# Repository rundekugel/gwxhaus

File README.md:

# gwxhaus
## Greenhouse Controller

*It's just started, not finished.*

Open hardware and firmware to control a greenhouse heating and cooling. Depends on temperature, humidity, wind and time.

An ESP32 controls the motor-controller and reads sensor data.

### Sensors
- Temperature in/out
- Humidity in/out
- Wind
- Soil moisture

There can be a lot of settings depending on sensor values and time.

### Actors
- Motors to open/close the windows
- Valves to control water
- Relais to control heating

The ESP32 is connected via another ESP32, ESP8266 or RaspberryPi to the WWW. Via mqtt the sensor data and actor positions are stored in a database and can be viewd in charts.

Optional, password protected, it's possible to change the settings and manually control the actors.

If any sensor values are out of range, or power fails, there can be messages sent via email, telegram, SMS, telephone (voip), or other channels.

Weather forecast data from Deutscher Wetterdienst https://dwd.api.bund.dev/ can be used to protect windows against storm or hail.

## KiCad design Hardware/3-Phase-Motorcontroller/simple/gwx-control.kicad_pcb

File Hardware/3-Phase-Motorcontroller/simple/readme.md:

# gwx-control-motor
## Simple motor controller

Created to control a 3 phase motor to open/close windows of a greenhouse
Created with Eagle Version 7.7

Features:
- switch off motor, if window arrived at end position 
- stop for about 3 seconds, if direction changes, to prevent too high current, which could destroy power switches.

Input: 
- motor on/off
- up/down
- switches for end positions

Output:
- +/- for optocoupler of power motor switcher. Can control DC and AC, 1 to 3 phase motors.
- +/- for direction switch relais

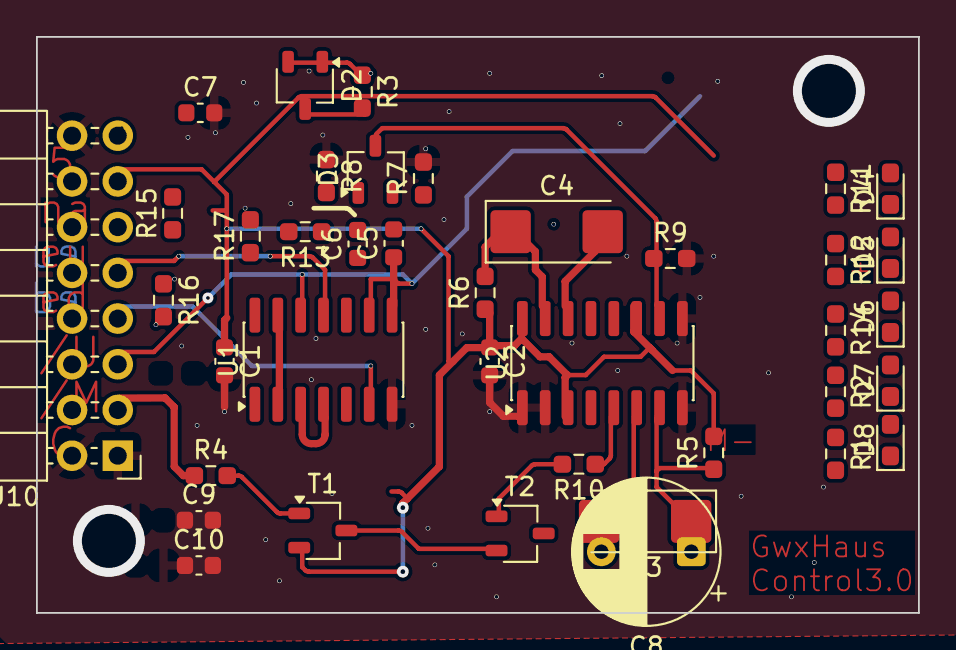
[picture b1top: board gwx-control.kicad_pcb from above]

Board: 2 copper layers, 49.0 x 32.0 mm, 39 parts (0 on the bottom side), 23 nets.

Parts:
C1, C2, C9, C10: 100n; C_0603_1608Metric
C3, C4: 47µ; CP_EIA-6032-28_Kemet-C_HandSolder
C5, C6: 1n; C_0603_1608Metric
C7: 1µF; C_0603_1608Metric
C8: 47µ; CP_Radial_D8.0mm_P5.00mm
D2, D3: BAT54C; TSOT-23
D4, D5, D6, D7, D8: LED_ESML0603; LED_0603_1608Metric_Pad1.05x0.95mm_HandSolder
J10: Conn_02x08_Odd_Even; PinHeader_2x08_P2.54mm_Horizontal
R1, R2, R3, R11, R12, R13, R14, R17: 4k7; R_0603_1608Metric_Pad0.98x0.95mm_HandSolder
R4, R7, R8, R10: 10k; R_0603_1608Metric_Pad0.98x0.95mm_HandSolder
R5, R9: 47k; R_0603_1608Metric_Pad0.98x0.95mm_HandSolder
R6: R-EU_R0603; R_0603_1608Metric_Pad0.98x0.95mm_HandSolder
R15, R16: 100R; R_0603_1608Metric_Pad0.98x0.95mm_HandSolder
T1, T2: BC850; TSOT-23
U1: 74LS02; SOIC-14_3.9x8.7mm_P1.27mm
U2: 74LS123; SOIC-16_3.9x9.9mm_P1.27mm

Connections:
/UP: C6.1, R13.1
//END_DOWN: C10.1, D8.1 (K), R16.1, U1.6
//END_UP: C9.2, D7.1 (K), R15.1, R17.1, U1.11
//MOTOR_OK: D5.1 (K), R10.1, U2.5 (Q)
//MOTOR_ON: D4.1 (K), J10.3, R4.1
//OK: J10.13, U1.1
//UP: C5.1, D2.1 (A1), D2.2 (A2), D6.1 (K), J10.5, R3.1, U1.8, U1.9, U1.12
GND: C1.2, C2.2, C7.2, C9.1, C10.2, J10.1, J10.2, J10.16, R7.2, R8.1, R9.2, U1.7 (GND), U2.1 (A), U2.2 (B), U2.8 (GND), U2.9 (A)
unnamed: C5.2, C6.2, R7.1, R8.2
unnamed: D3.3 (CC), R9.1, U2.10 (B)
unnamed: D4.2 (A), R11.1
unnamed: D5.2 (A), R12.1
unnamed: D6.2 (A), R14.1
unnamed: D7.2 (A), R2.1
unnamed: D8.2 (A), R1.1
unnamed: J10.7, R16.2
unnamed: J10.9, R15.2
unnamed: U1.3, U1.4
unnamed: U1.5, U1.10
unnamed: U1.2, U1.13
unnamed: R6.2, U2.15 (RCext)
unnamed: R5.1, U2.7 (RCext)
VCC: C1.1, C2.1, C7.1, D2.3 (CC), J10.15, R1.2, R2.2, R3.2, R5.2, R6.1, R11.2, R12.2, R13.2, R14.2, R17.2, U2.11 (Clr), U2.16 (VCC)

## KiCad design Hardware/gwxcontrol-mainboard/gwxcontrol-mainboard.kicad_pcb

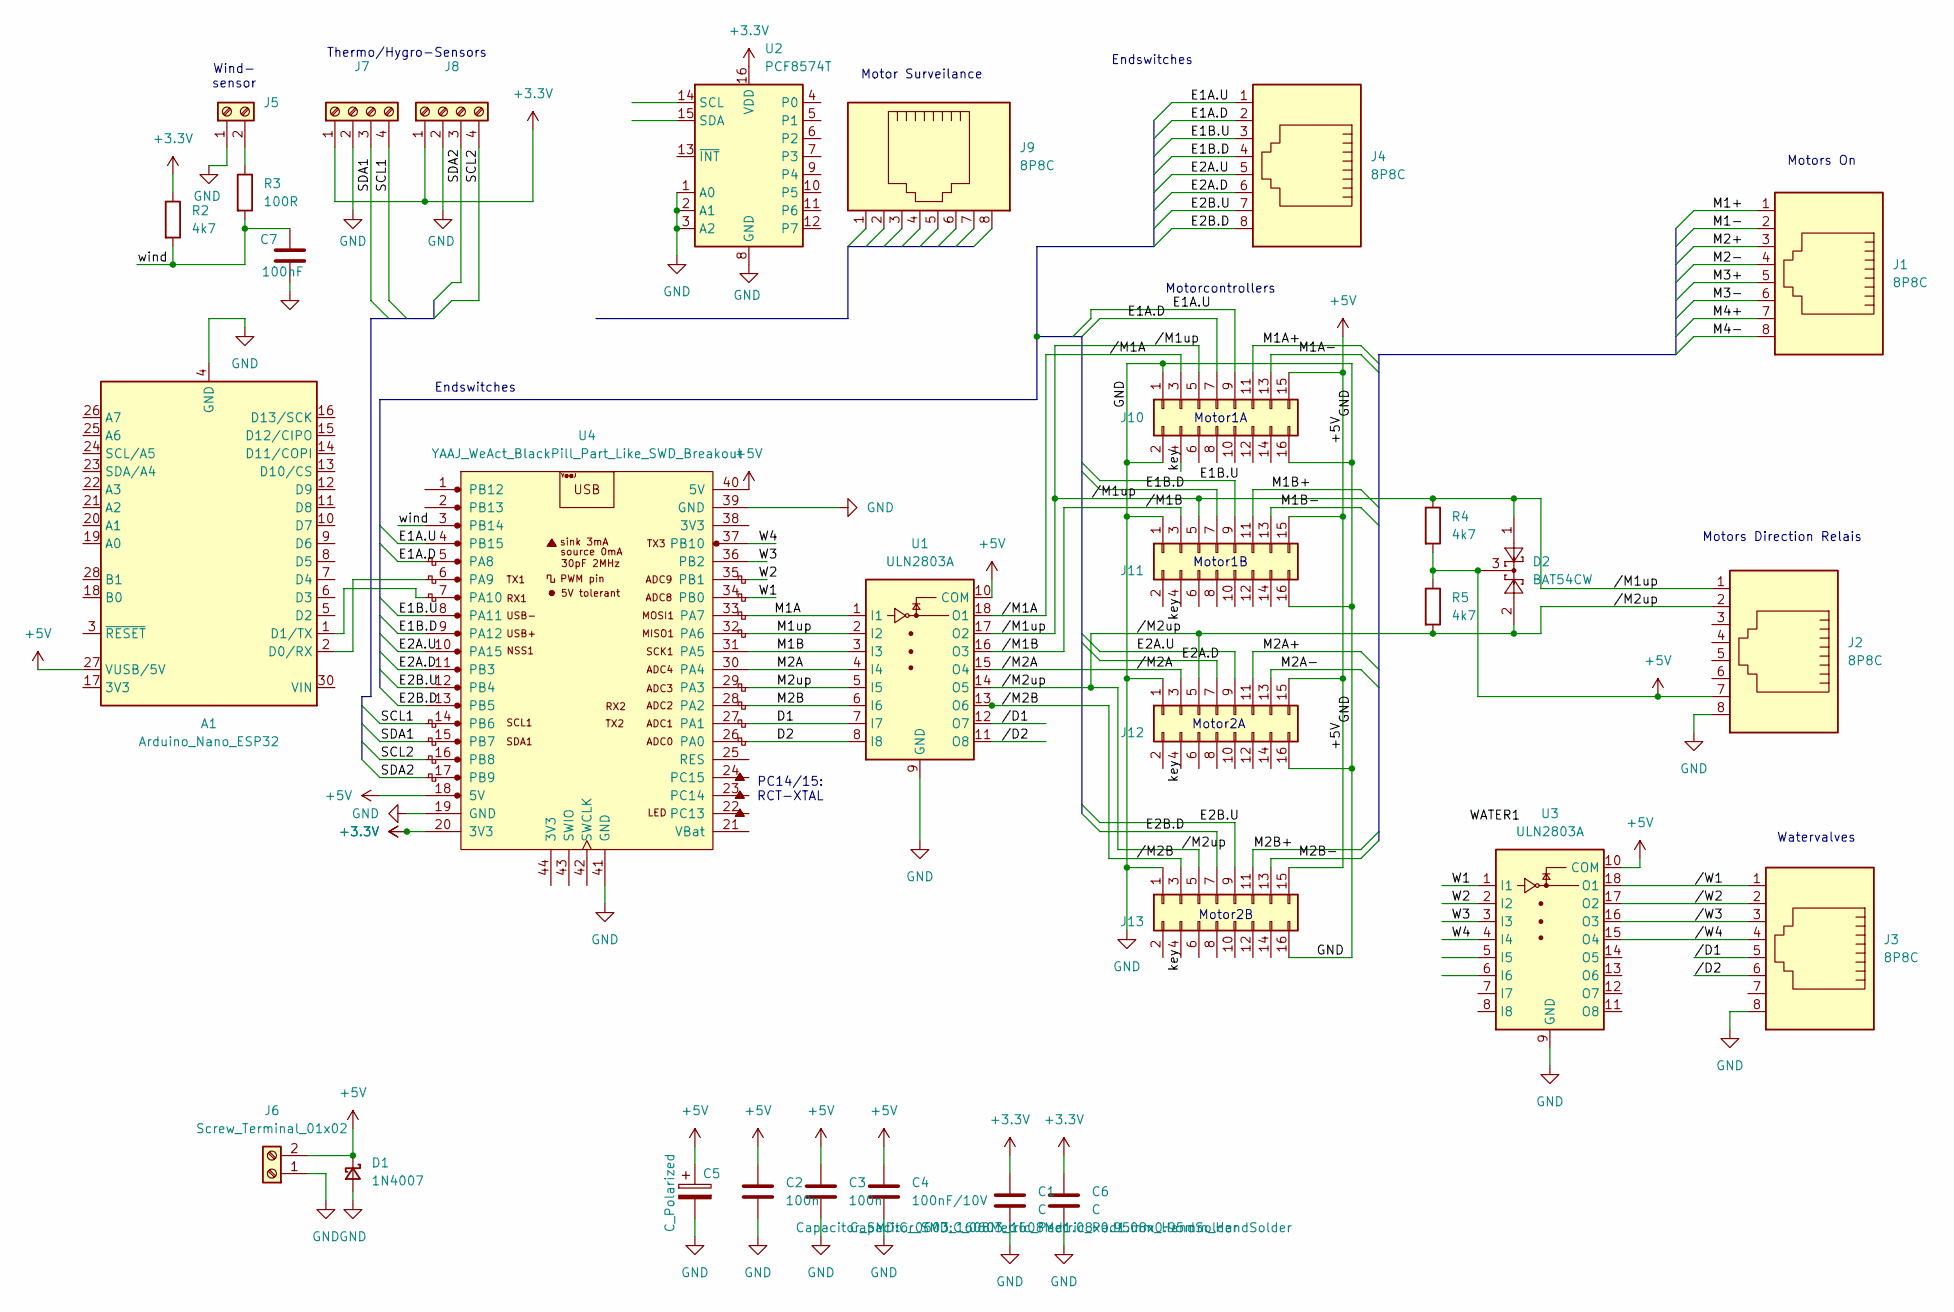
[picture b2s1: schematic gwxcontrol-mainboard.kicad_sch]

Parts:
A1: Arduino_Nano_ESP32; Arduino_Nano
C1, C6: C; C_0603_1608Metric_Pad1.08x0.95mm_HandSolder
C2, C3: 100n; C_0603_1608Metric_Pad1.08x0.95mm_HandSolder
C4: 100nF/10V; C_0603_1608Metric_Pad1.08x0.95mm_HandSolder
C5: C_Polarized; CP_Radial_D12.5mm_P5.00mm
C7: 100nF; C_0603_1608Metric_Pad1.08x0.95mm_HandSolder
D1: 1N4007; D_DO-41_SOD81_P10.16mm_Horizontal
D2: BAT54CW; SOT-323_SC-70
J1, J2, J3, J4, J9: 8P8C; RJ45_Plug_Metz_AJP92A8813
J5, J6: Screw_Terminal_01x02; TerminalBlock_Phoenix_PTSM-0,5-2-2.5-H-THR_1x02_P2.50mm_Hor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
J7, J8: Screw_Terminal_01x04; TerminalBlock_Phoenix_PTSM-0,5-4-2.5-H-THR_1x04_P2.50mm_Hor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
J10, J11, J12, J13: Conn_02x08_Odd_Even; PinSocket_2x08_P2.54mm_Vertical
R2, R4, R5: 4k7; R_0603_1608Metric_Pad0.98x0.95mm_HandSolder
R3: 100R; R_0603_1608Metric_Pad0.98x0.95mm_HandSolder
U1, U3: ULN2803A; DIP-18_W7.62mm_LongPads
U2: PCF8574T; SOIC-16W_7.5x10.3mm_P1.27mm
U4: YAAJ_WeAct_BlackPill_Part_Like_SWD_Breakout; YAAJ_WeAct_BlackPill_2

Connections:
+3.3V: C1.1, C6.1, J7.1, J8.1, R2.1, U2.16 (VDD), U4.20 (3V3)
+5V: A1.27 (VUSB/5V), C2.1, C3.1, C4.1, C5.1, D1.1 (K), D2.3, J2.7, J6.2, J10.15, J11.15, J12.15, J13.15, R4.2, R5.1, U1.10 (COM), U3.10 (COM), U4.18 (5V), U4.40 (5V)
/D1: U1.7 (I7), U4.27 (PA1)
/D2: U1.8 (I8), U4.26 (PA0)
/E1A.D: J4.2, J10.7, U4.5 (PA8)
/E1A.U: J4.1, J10.9, U4.4 (PB15)
/E1B.D: J4.4, J11.7, U4.9 (PA12)
/E1B.U: J4.3, J11.9, U4.8 (PA11)
/E2A.D: J4.6, J12.7, U4.11 (PB3)
/E2A.U: J4.5, J12.9, U4.10 (PA15)
/E2B.D: J4.8, J13.7, U4.13 (PB5)
/E2B.U: J4.7, J13.9, U4.12 (PB4)
/M1+: J1.1
/M1-: J1.2
/M1A: U1.1 (I1), U4.33 (PA7)
/M1A+: J10.11
/M1A-: J10.13
/M1B: U1.3 (I3), U4.31 (PA5)
/M1B+: J11.11
/M1B-: J11.13
/M1up: U1.2 (I2), U4.32 (PA6)
/M2+: J1.3
/M2-: J1.4
/M2A: U1.4 (I4), U4.30 (PA4)
/M2A+: J12.11
/M2A-: J12.13
/M2B: U1.6 (I6), U4.28 (PA2)
/M2B+: J13.11
/M2B-: J13.13
/M2up: U1.5 (I5), U4.29 (PA3)
/M3+: J1.5
/M3-: J1.6
/M4+: J1.7
/M4-: J1.8
/SCL1: J7.4, U4.14 (PB6)
/SCL2: J8.4, U4.16 (PB8)
/SDA1: J7.3, U4.15 (PB7)
/SDA2: J8.3, U4.17 (PB9)
/W1: U3.1 (I1), U4.34 (PB0)
/W2: U3.2 (I2), U4.35 (PB1)
/W3: U3.3 (I3), U4.36 (PB2)
/W4: U3.4 (I4), U4.37 (PB10)
/key: J10.4
/wind: C7.2, R2.2, R3.2, U4.3 (PB14)
//D1: J3.5, U1.12 (O7)
//D2: J3.6, U1.11 (O8)
//M1A: J10.3, U1.18 (O1)
//M1B: J11.3, U1.16 (O3)
//M1up: D2.1, J2.1, J10.5, J11.5, R4.1, U1.17 (O2)
//M2A: J12.3, U1.15 (O4)
//M2B: J13.3, U1.13 (O6)
//M2up: D2.2, J2.2, J12.5, J13.5, R5.2, U1.14 (O5)
//W1: J3.1, U3.18 (O1)
//W2: J3.2, U3.17 (O2)
//W3: J3.3, U3.16 (O3)
//W4: J3.4, U3.15 (O4)
GND: A1.4 (GND), A1.29 (GND), C1.2, C2.2, C3.2, C4.2, C5.2, C6.2, C7.1, D1.2 (A), J2.8, J3.8, J5.1, J6.1, J7.2, J8.2, J10.1, J10.2, J10.16, J11.1, J11.16, J12.1, J12.16, J13.1, J13.16, U1.9 (GND), U2.1 (A0), U2.2 (A1), U2.3 (A2), U2.8 (GND), U3.9 (GND), U4.19 (GND), U4.39 (GND), U4.41 (GND)
unnamed: A1.2 (D0/RX), U4.6 (PA9)
unnamed: A1.1 (D1/TX), U4.7 (PA10)
unnamed: J5.2, R3.1

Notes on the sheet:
Endswitches
Watervalves
Wind- sensor
Thermo/Hygro-Sensors
Motors Direction Relais
Motor1A
Motor Surveilance
Motor2B
Motorcontrollers
PC14/15: RCT-XTAL
Motor1B
Motors On
Motor2A

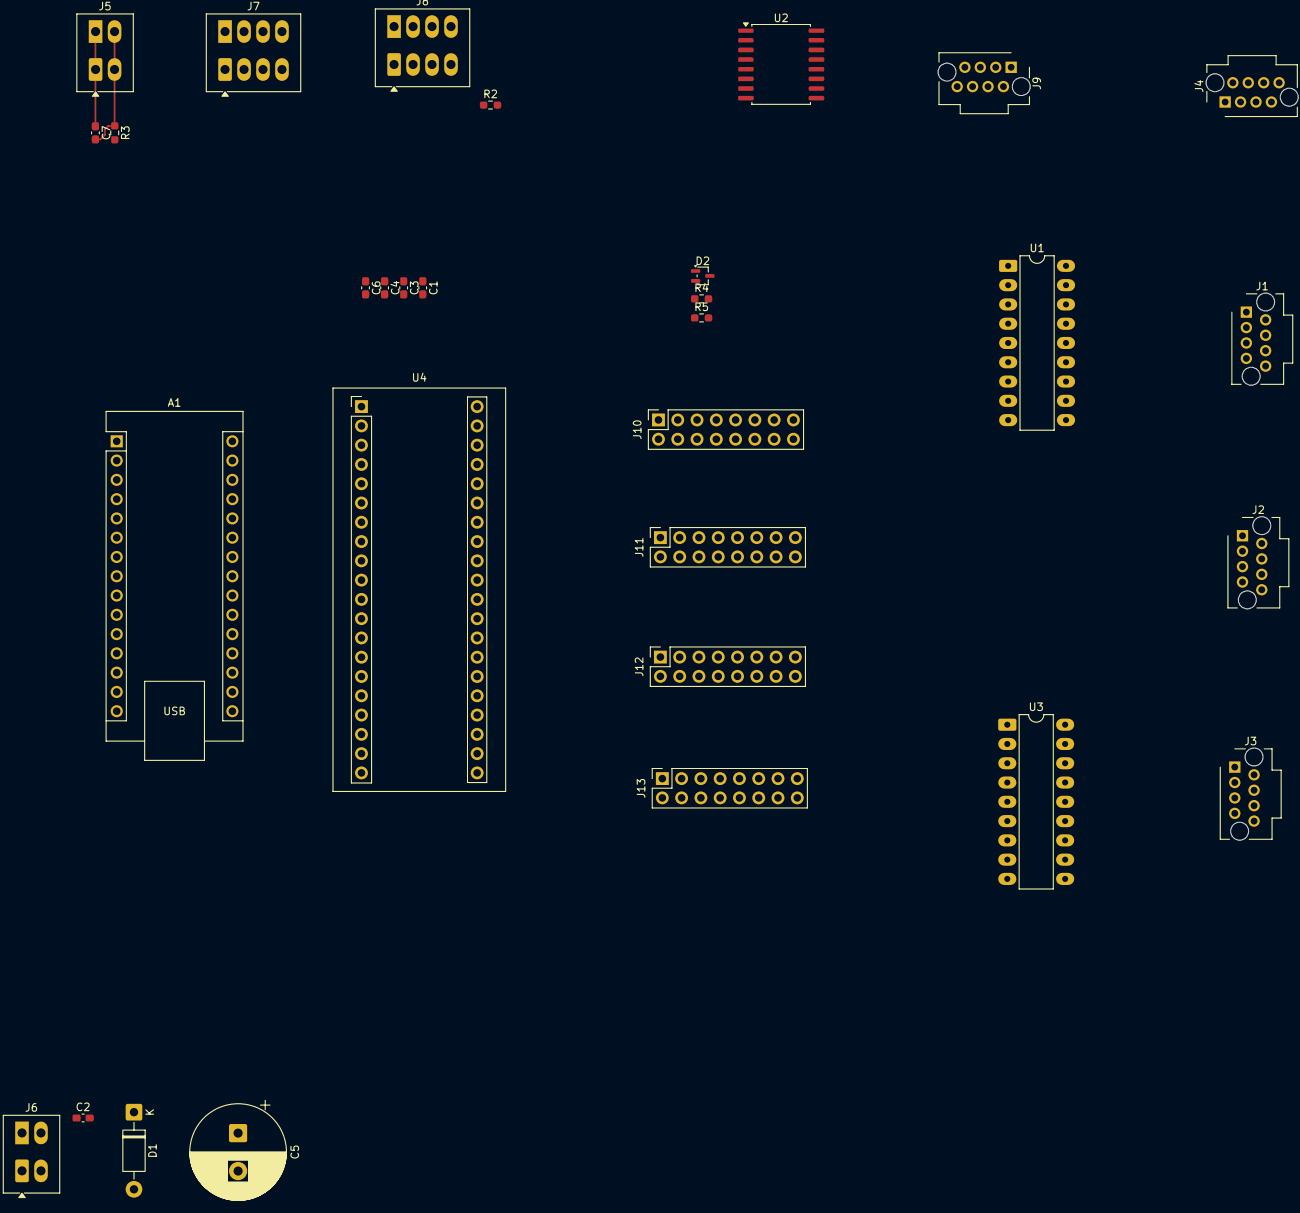
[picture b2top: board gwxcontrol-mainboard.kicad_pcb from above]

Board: 2 copper layers, 31 parts (0 on the bottom side), 43 nets.

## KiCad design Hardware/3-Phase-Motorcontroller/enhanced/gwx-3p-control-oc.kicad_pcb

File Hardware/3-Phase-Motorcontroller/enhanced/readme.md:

# gwx-control-motor-oc
## Enhanced motor controller

Created to control a 3 phase motor to open/close windows of a greenhouse. 
Created with Eagle Version 7.7

Features:
- switch off motor, if direction changes
- switch off motor, if window arrived at end position 

Input: 
- motor on/off
- up/down
- switches for end positions. Optocoupler protected. 

Output:
- +/- for optocoupler of motorswitcher. Can control DC and AC, 1 to 3 phase motors.
- +/- for direction switch relais.

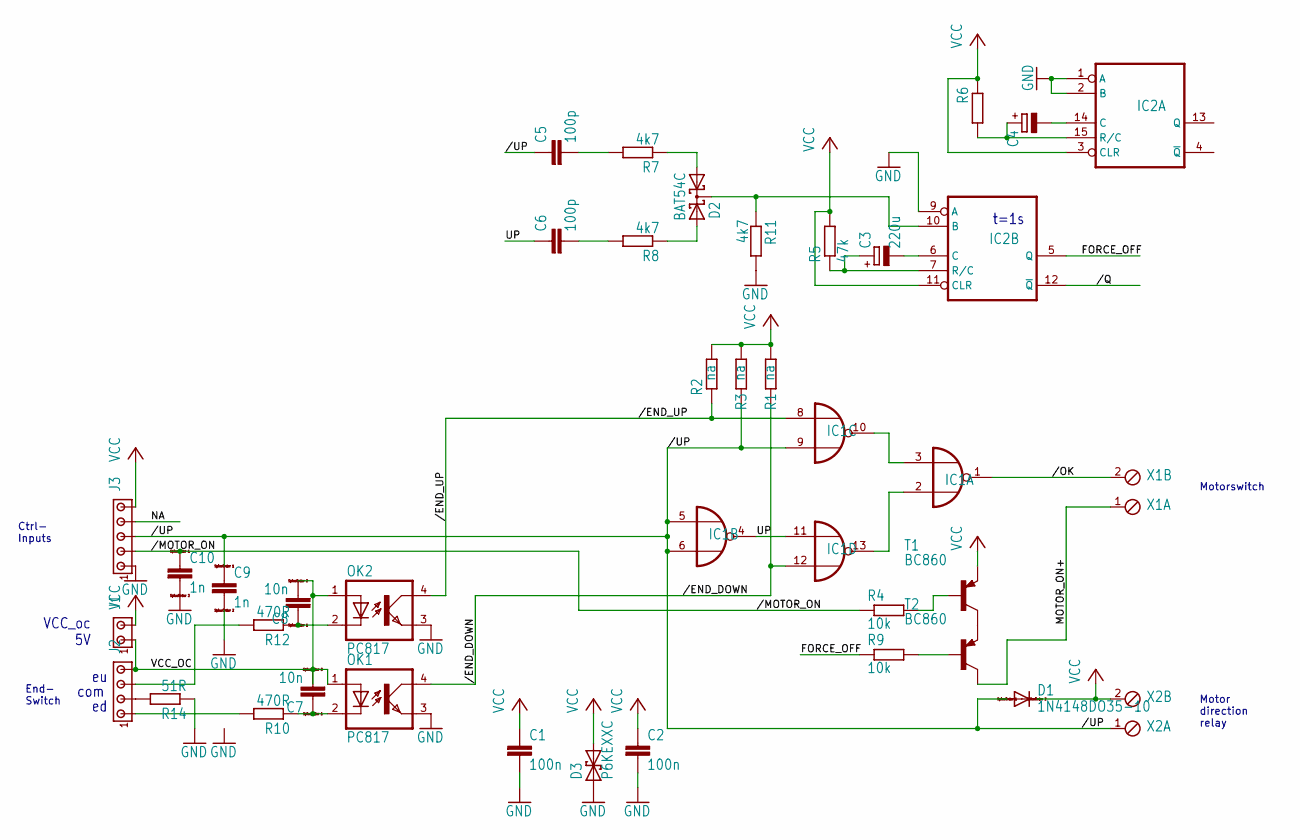
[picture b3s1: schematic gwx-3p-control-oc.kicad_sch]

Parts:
C1, C2: 100n; C0603K
C3: 220u; E5-6
C4: CPOL-EUE5-6; E5-6
C5, C6: 100p; C0603K
C7, C8: 10n; C0603
C9, C10: 1n; C0603
D1: 1N4148DO35-10; DO35-10
D2: BAT54C; SOT23
D3: P6KEXXC; CB417-15
IC1: 7402D; SO14
IC2: 74123D; SO16
J1: MTA02-100; 10X02MTA
J2: MTA04-100; 10X04MTA
J3: MTA05-100; 10X05MTA
OK1, OK2: PC817; DIL04
R1, R2, R3: na; R0603
R4, R9: 10k; R0603
R5: 47k; R0603
R6: R-EU_R0603; R0603
R7, R8, R11: 4k7; R0603
R10, R12: 470R; R0603
R14: 51R; R_0603_1608Metric
T1, T2: BC860; SOT23-BEC
X1, X2: MPT2; 2POL254

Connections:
/ED: J2.1, R10.2
/END_DOWN: IC1.12 (I1), OK1.4 (COL), R1.1
/END_UP: IC1.8 (I0), OK2.4 (COL), R2.1
/EU: J2.3, R12.2
/MOTOR_ON: C10.1, J3.2, R4.1
/OK: IC1.1 (O), X1.2
/Q: IC2.12 (~Q)
/UP: C5.1, C9.1, D1.A, IC1.5 (I0), IC1.6 (I1), IC1.9 (I1), J3.3, R3.1, X2.1
ECOM: J2.2, R14.2
FORCE_OFF: IC2.5 (Q), R9.1
GND: C1.2, C2.2, C9.2, C10.2, D3.A (1), IC1.7 (GND), IC2.1 (A), IC2.2 (B), IC2.8 (GND), IC2.9 (A), J3.1, OK1.3 (EMIT), OK2.3 (EMIT), R11.2, R14.1; also elsewhere on the board
MOTOR_ON+: T2.C, X1.1
unnamed: C3.+, IC2.7 (R/C), R5.1
unnamed: C3.-, IC2.6 (C)
unnamed: C4.+, IC2.15 (R/C), R6.2
unnamed: C5.2, R7.2
unnamed: IC1.3 (I1), IC1.10 (O)
unnamed: IC1.2 (I0), IC1.13 (O)
unnamed: C6.2, R8.2
unnamed: D2.3 (CC), IC2.10 (B), R11.1
unnamed: C4.-, IC2.14 (C)
unnamed: R4.2, T1.B
unnamed: R9.2, T2.B
unnamed: T1.C, T2.E
unnamed: D2.1 (A1), R7.1
unnamed: C7.1, OK1.2 (C), R10.1
unnamed: C8.1, OK2.2 (C), R12.1
unnamed: D2.2 (A2), R8.1
UP: C6.1, IC1.4 (O), IC1.11 (I0)
VCC: C1.1, C2.1, D1.C, D3.C (2), IC1.14 (VCC), IC2.3 (CLR), IC2.11 (CLR), IC2.16 (VCC), J1.2, J3.5, R1.2, R2.2, R3.2, R5.2, R6.1, T1.E, X2.2
VCC_OC: C7.2, C8.2, J1.1, J2.4, OK1.1 (A), OK2.1 (A)

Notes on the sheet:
VCC_oc 5V
Motorswitch
com
Motor direction relay
End- Switch
t=1s
Ctrl- Inputs

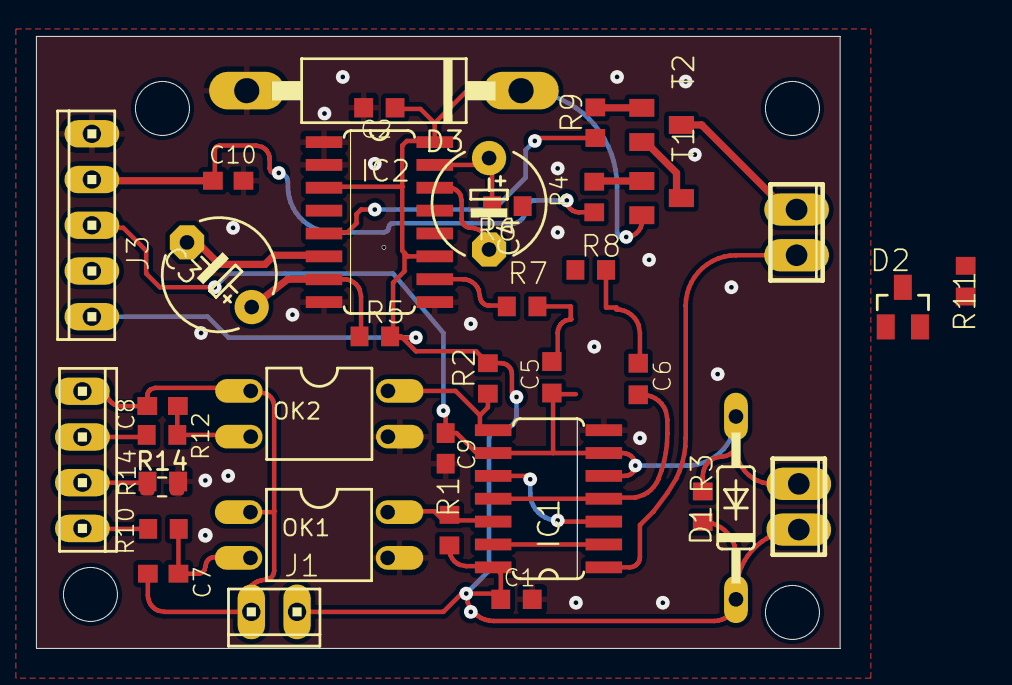
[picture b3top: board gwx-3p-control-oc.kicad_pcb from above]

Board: 2 copper layers, 44.6 x 34.0 mm, 42 parts (0 on the bottom side), 30 nets.

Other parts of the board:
@HOLE0, @HOLE1, @HOLE2, @HOLE3: (no value)
R14#2: 51R; R_0603_1608Metric

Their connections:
GND: R14#2.1; also elsewhere on the board

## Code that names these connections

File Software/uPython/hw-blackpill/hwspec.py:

# Hardware specific pin configuration for blackpill 
HW_SPEC = "HW BluePill Spec 0.1"

# --- Info ---
# PA11/12 are USB D-/+
# PA10 ID (optional)
# PA9 USB Sense (optional)
# -------------

# USART PA2/3

PIN_WIND = "PB14" 
PIN_SCL1 = "PB6"
PIN_SDA1 = "PB7"
PIN_SCL2 = "PB8"
PIN_SDA2 = "PB9"
PIN_NUM_LED1 = "PC13"

PINS_NUM_WATER = ("PB13", "PB12", "PB2", "PB10")

PIN_NUM_MOTOR1 = "PA7"   # hi=on
PIN_NUM_MOTOR1B = "PA5"   # hi=on
PIN_NUM_MOTOR1D = "PA6"  # hi=up
PIN_NUM_MOTOR2 = "PA4"   # hi=on
PIN_NUM_MOTOR2B = "PA2"   # hi=on
PIN_NUM_MOTOR2D = "PA3"  # hi=up

# Endswitches (UP,DOWN) - low active
PINS_NUM_END = (
    ("PB15","PA8"),    #1A
    ("PA11","PA12"),   #1B
    ("PA15","PB3"),    #2A
    ("PB4", "PB5")     #2B
)


DOSEN_NUM = ("PA1","PA0")

PIN_ADC_BATT = None # "PB0"
PINNUM_POWER = None # "PB1"   # needed for wakeup

PIN_BUTTON1 = "PA0"

UART_NUM = 1

    # VP
# pins PC14/15 are xtal32

# eof

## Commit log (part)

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2024-04-23 first draft
2024-04-23 added power switch protection
    motor will stop for a few seconds, if direction changes
2024-04-23 doc changed
2024-04-23 more info
2024-04-23 added direction changer brd
2024-05-01 Trigger fixed
2024-05-01 force motor off is now more relyable
    changed from pull down the base of t1 to active switch a 2n T in series
2024-05-01 Changed Motor force off to non inverted mono flop output
2024-05-01 added alternative SMD diode
2024-05-01 pcb size cahnged to 33x54
2024-05-01 LEDs added
2024-05-12 Motor out sign fixed (+)==>(-)
2024-05-13 reading of humidity sensor HYT-221 in µPython
2024-05-13 more doc / mock up
2024-05-13 i2c works now also for ESP32
2024-05-24 Version info added
2024-05-24 HYT221 changed to class, to support multiple sensors
2024-05-24 mocked up
2024-05-25 initial windsensor class for pulse wind sensors
2024-05-25 destructor for irq handler
2024-05-25 simple tcp server
2024-05-25 round values
2024-05-25 prepared for 2 sensors
2024-05-25 prepared seperate files simpleserv and gwxcrlk
2024-05-25 exchanged wifi with uart for core controller
    uart is more stable.
2024-05-25 set/get motor state prepared
2024-05-25 RTC added
2024-05-25 read config added
2024-05-25 cfg is parsed. cfg not case-sensitive, now
    all cfg is overwritten lower case
    getTime() with optional offset for timer
2024-05-26 testmode remote control for HYT221 implemented
2024-05-26 setMotor() parsing fix
2024-05-26 buffer multiple messages
2024-05-26 init pins with 0
2024-05-26 set water timer only, if needed
2024-05-26 fixed quotes
2024-05-26 new cmd: get todos
    new cmd: get todos : "todos?"
    tolerate string in globs.rx for easier todo-construction
2024-05-26 windsensor value can be overwritten for tests
2024-05-26 windsensor pin changed. motor id typo fix.
2024-05-26 typo fix
2024-05-26 option to change verbosity
2024-05-26 hyt221 uses default addr, if addr is None
2024-05-26 HYT221 address can be set per config
2024-05-26 set rtc possible
2024-05-26 cmd "reset!" added
2024-05-27 windsensor param for rounded values
2024-05-27 support deepsleep for ESP32
2024-05-27 Battery Voltage and power supply readable
2024-05-27 ADC calc adjusted to hardware voltage divider
2024-05-27 ligtsleep on power loss, deep sleep on low batt voltage
2024-05-27 parser simplified
2024-05-28 mock up
2024-06-06 init happens in main
2024-06-06 set rtc works with less params
2024-06-09 new pins
2024-06-10 pinning for esp32-light
2024-06-10 degree symbol broke uart data sending
2024-06-30 dose1/2 added
2024-06-30 aes implemented
2024-06-30 crypto-stuff in extra file
2024-06-30 remove secrets before tx
2024-07-01 fix for json compatibility
2024-07-01 sensor data in html table
2024-07-01 less logs
2024-07-01 avoid spamming html page with error messages
2024-07-02 wind speed without thousands of post decimal positions
    and controller temp display although TH-sensor not available
2024-07-02 added km/h to GUI
    don't try to parse Error 504 or empty message
2024-07-04 decryptor moved. i2cscan added.
2024-07-04 mock up
    hyt221 init lean
    docrypt shows version on start
2024-07-07 i2c freq. lower
    try to solve "sensor not found"
2024-07-07 stylesheet and tables added
2024-07-07 Kommentar
2024-07-07 css more green
2024-07-29 modcfg added
2024-07-31 Fix show humidity value for sensor1
2024-07-31 added config of sensor frequency
2024-08-09 table closing row fix
2024-08-09 New: voltage supply monitor for 3 phases
2024-08-13 formatting changed
2024-08-15 watchdog added
2024-08-15 added a voltage calc divider
2024-08-17 using preloaded mqtt msg, now
2024-08-17 mockup
2024-08-17 wind display fix; mockup
2024-08-17 added mqttbuf-service config file
2024-08-17 mqttbuf-service changed for config-file
2024-08-17 more debug features
2024-09-03 new cmd: manually
2024-09-03 disabled unallowed pin
2024-09-04 using parameter filename instead of taskname for the temporary file
2024-09-06 accept some baudrates for comu.init()
2024-09-06 don't show secret config values
2024-09-06 windsensor.init() accept None for diameter
2024-09-06 less verbose
2024-09-06 can set diameter via cfg
2024-09-18 wdt init int fix
2024-09-18 simple login demo added
2024-09-18 motor buttons added
2024-09-18 simple test ==> simple table
2024-09-19 tcp2mqtt.py added
2024-09-19 translator for old fw short key (m1) ==> long (motor1)
2024-09-19 tcp2mqtt config template added
2024-09-19 tcp2mqtt rx-port configurable
2024-09-19 config file can overwrite global vars
2024-09-20 hide buttons, if not authorized
2024-09-20 buttons format
2024-09-21 end switch feature
    calculate a virtual model of window angle by time of motor state on
    windsensor prop fac. added
2024-09-21 checkendswitch py==>uPy
2024-09-21 water keyword Wassern ==> Wn
2024-09-21 added keywords for water 1..4 and virtually window state
2024-09-21 new keywords for states of motor, windows, temp. and humidity
    for motors' and windows' state
2024-09-22 added login and buttons to tec1
2024-09-22 tec1 can display globs and cfg
2024-09-22 switcher can use globs and cfg
2024-09-22 Warnung bei Unterspannung
2024-09-22 windsensor filter changed to windowed sorted filter
2024-09-22 water timetable with 1 minute resolution
2024-09-23 watertables index fix
    + avoid publish SECRET_GLOBS
2024-09-23 set RTC added to tec1
2024-09-23 added keyword RTC to switcher
2024-09-23 rtc added to tcp2mqtt.service
2024-09-23 updated manuell buttons
2024-09-23 neu: sturm warnung
2024-09-23 update config via mqtts
2024-09-23 new parameters: mqtt topic rx/tx
2024-09-23 on too high humidity, close window only, if temperature is < max
2024-09-23 more parameters
    -k=<key> change/add this key
    -d=<data> set data
    -dn=<number> set data as number, without quotes.
    -t=<text> send this text
2024-09-23 deal with wrong value in "globs.verbosity"
2024-09-23 resttime ist humanreadable, now
2024-09-23 zisterne prepared
2024-09-23 water time table configurator
2024-09-23 version inc
2024-09-23 changed str_contains() for php7
2024-09-23 2 tables for demo
2024-09-24 fixed some typos; mockup
2024-09-24 typo fixed
2024-09-25 empty val error fix.val init str/bytes fix
2024-09-26 parse key USB fix for voltage display
2024-10-17 configfile option for updateconfig.py
2024-10-29 updateconfig fix for float values
2024-11-18 html anchors
2024-11-18 tmp file erased
2024-12-23 small fixes
2024-12-26 anleitung
2024-12-26 anleitung added
2024-12-26 manuell state longer duration
2024-12-26 tiny, but powerful design enhancement
2024-12-26 undo deletion of needed tcp2mqtt.py
2024-12-26 switch manually js fix
2024-12-26 with graphic
2025-03-15 added param -js to send config as file
2025-03-15 prepared for more dose
2025-03-21 prevent watchdog from to short intervals
    wdttime default= 90
    minimum= 30
2025-03-21 fixed typo
2025-03-21 readConfig() made failsafe
2025-03-21 avoid crash, if haus-vars missing
2025-03-21 added debug support and new cmd: delcfg
2025-03-28 wifi sockets added
2025-03-29 added more handlers for webpage infos
2025-03-29 one handler to handle multiple nous
2025-03-30 more info for funksteckdosen
2025-03-30 more color for ui
2025-03-30 formating of funkdosenstatus
    tools: byId() ; splitOnce()
    style: beauty up
    tec1: FunkDosenNamen
2025-03-30 motor halb feature prepared
2025-04-05 update blocksize variable
2025-04-05 delete buffer after "modcfg.", even if error
    loop_sleep reduced, we are slow enough.
2025-04-05 prepared for half window position
2025-04-05 doMotors() added to support half position of window
2025-04-05 window close on storm changed
2025-04-05 checkTemp() upgraded to globs.window_pos_dest instead of direct setMotor
2025-04-05 fixed: window goes up if position negative
2025-04-06 motordelay implemented
    if one window at endposition let the other motor run one more second
2025-04-06 motor/fenster cmd can be 0-100 and u,d,h,s
    fenster destination can be:
    (u)p, (d)own, (s)stop, (h)alf.
    or any integer. alowed is only 0-100 !
2025-04-06 tcp2mqtt: param -v for verbosity added
2025-05-02 added schematic as pdf
2025-05-02 gwx-control-simple pcb and sch as pdf added
2025-05-06 Parameter handling changed
2025-05-06 checkWindowPosition_lastTime moved to globs to work also for older python-versions
2025-05-10 watchTimeout added for alert messages if mqtt-LWT
2025-05-10 send alarm only, if not again online after small time
2025-05-10 topics fix
2025-05-10 moved services to new folder server-services
2025-05-31 more features
    + configfile
    + controltopic
    + enable/disable topics
2025-05-31 config modified
    some params stored in watchTimeout.cfg
    only credentials in credentials.dat
2025-05-31 human readable device names
2025-05-31 interval configurable; mockup
2025-05-31 msgdelaytime added to allowed key for config
2025-06-18 more doc
2025-06-18 init dosen. more doc
2025-06-18 timeout watcher for mqtt-LWL added
2025-06-18 changed back to UTF-8
2025-06-18 git revision added to version string
2025-06-20 motor cmd '0' ==> 's'
2025-06-20 USE_END_SWITCHES deactivated, until they are connected
2025-06-20 msg-box deactivated
2025-06-20 setmotor params more compatible: can be : d,u,s,0
2025-06-20 wachTimeout.cfg as default
2025-06-20 more config demo
2025-06-20 prechecked checkbox
2025-06-20 added watertable 3+4
2025-06-20 added: read confg from watertable
2025-06-22 waits added, for direction switch relais.
2025-06-22 uart uses flush, before write
2025-06-24 updateconfig.py works for json-config-files
    json-config files are uploaded, also if no key is given
    gwxcontrol.py: doc updated
2025-06-24 alarm for min. temp added
    comu: ignore, if uart.flush not available
2025-07-13 datetime timezone set to berlin
2025-07-13 fixed cmd receiver
2025-07-13 more feedback for cmds
2025-07-13 versioninfo added to info-cmd
2025-08-04 changed commands from bytearray to string
2025-08-04 added gitignore
2025-08-04 fixed typo time_ms => sleep_ms
2026-02-15 fixed setting timezone
    some servers need additional command: time.tzset()
2026-02-15 updateconfig.cfg as default
2026-04-24 firmware version can be requested
2026-06-04 download watertable
2026-06-04 V0.0.3 json konfig upload/download
2026-06-04 rights check fix
2026-06-04 Mock up: Removed unused code.
2026-06-04 Config transfer button prepared
2026-06-09 kicad files added
2026-06-09 kicad project file
